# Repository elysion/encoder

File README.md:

# Interface module for modular controllers

The module can be used for converting encoder, pot and button movement
into messages sent over TWI / I2C. You can e.g. combine up to 6 encoders 
(with push buttons) and connect them to a single 
microcontroller (ATMega168p) using only two separate PCB designs. This 
helps to bring down the costs of the BOM and of the boards. The design 
also  includes a configurable LED ring that can be used to visualize the 
positions of the encoders. You can connect up to 112 microcontroller 
boards to a single bus to create a device with up to 672 encoders!

By connecting a USB enabled microcontroller to the I2C bus you can
create an UI for all kinds of devices such as musical instruments,
DJ controllers, home automation control panels, etc.

The PCBs are connected using FFC cables making building, reusing
reconfiguring and debugging the parts easy while at the same time
keeping the BOM cost low.

You can find a proof of concept programming jig / bed of nails tester
for the microcontroller board here: https://a360.co/2ylXmQ3

## Currently supported components and settings
* Encoders
  * Absolute / Relative
  * Loop around / constrained between values
* Potentiometers
* Single switches and 3x3 button matrices
* AT42QT1010 capacitive touch sensor
* Sparkfun 2x2 button pads with SMT LED
* SK6812 / WS2812 serially addressable LEDs

## Project status
* If you would like to use the designs and the code in your project, please add a issue to this repository
  so that I can check whether the needed features have been implemented.
* There have been multiple iterations of the PCBs and not all software has been updated to work on the
  latest PCBs. The current implementation uses the PCB_VERSION constant with value 3 in the code.
  * Features not updated currently:
    * Touch
    * Pads
    * Potentiometers
    * Button matrices (?)

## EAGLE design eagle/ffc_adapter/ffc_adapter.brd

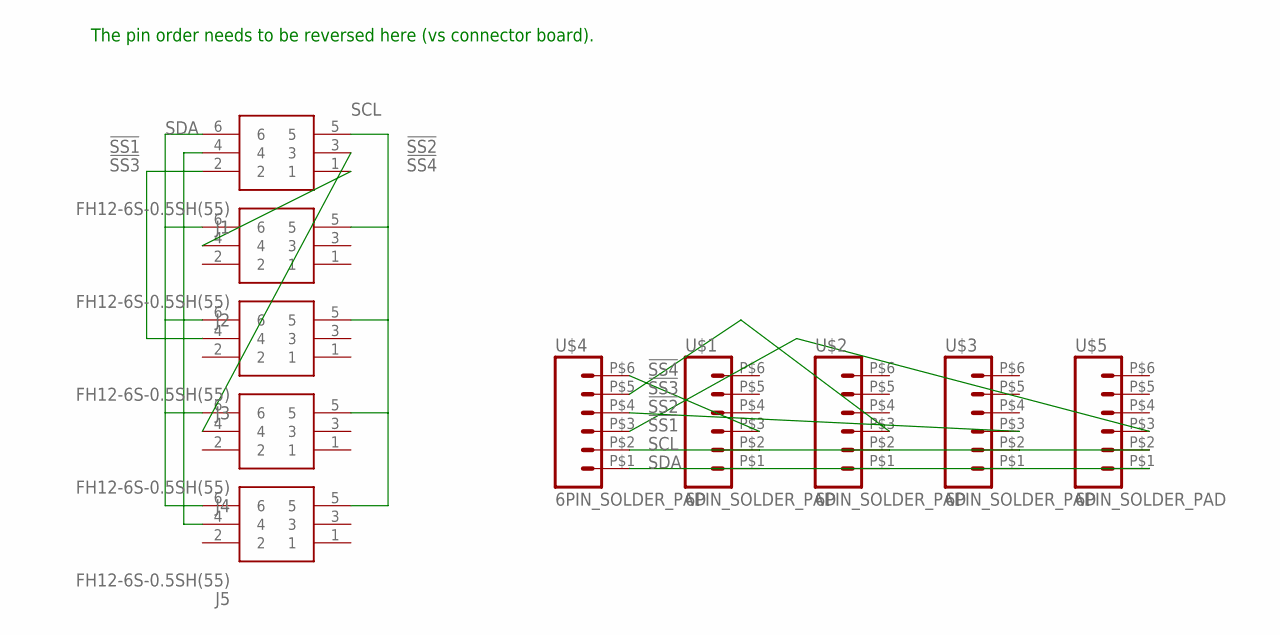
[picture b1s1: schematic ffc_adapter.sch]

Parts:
J1, J2, J3, J4, J5: FH12-6S-0.5SH(55); FH12-6S-0.5SH(55)_1
U$1, U$2, U$3, U$4, U$5: 6PIN_SOLDER_PAD

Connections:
!SS1: J1.4, J5.4, U$4.P$3 (3), U$5.P$3 (3)
!SS2: J1.3, J4.4, U$3.P$3 (3), U$4.P$4 (4)
!SS3: J1.2, J3.4, U$2.P$3 (3), U$4.P$5 (5)
!SS4: J1.1, J2.4, U$1.P$3 (3), U$4.P$6 (6)
SCL: J1.5, J2.5, J3.5, J4.5, J5.5, U$1.P$2 (2), U$2.P$2 (2), U$3.P$2 (2), U$4.P$2 (2), U$5.P$2 (2)
SDA: J1.6, J2.6, J3.6, J4.6, J5.6, U$1.P$1 (1), U$2.P$1 (1), U$3.P$1 (1), U$4.P$1 (1), U$5.P$1 (1)

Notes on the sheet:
The pin order needs to be reversed here (vs connector board).

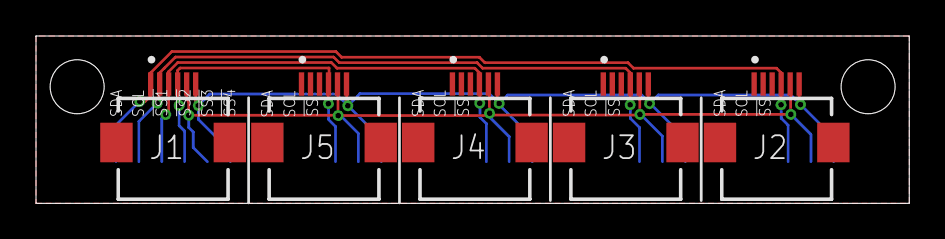
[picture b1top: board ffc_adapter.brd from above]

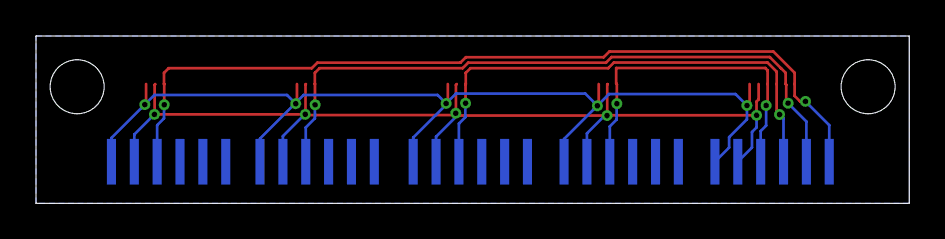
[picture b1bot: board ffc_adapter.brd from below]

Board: 2 copper layers, 48.5 x 9.3 mm, 10 parts (5 on the bottom side), 6 nets.

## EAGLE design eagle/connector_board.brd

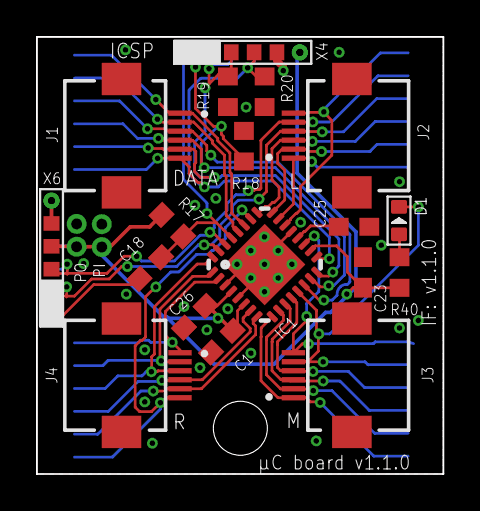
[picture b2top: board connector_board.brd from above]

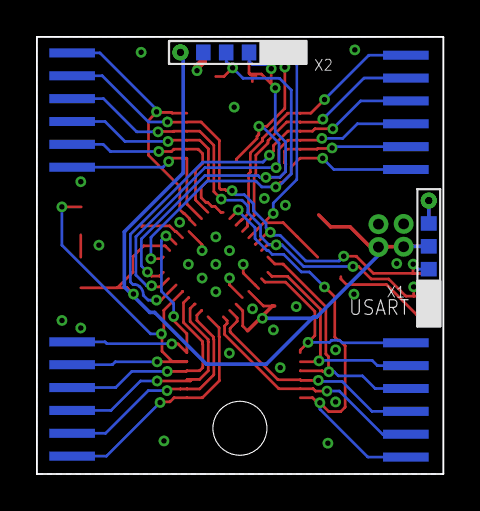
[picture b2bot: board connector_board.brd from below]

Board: 2 copper layers, 22.6 x 24.3 mm, 28 parts (6 on the bottom side), 32 nets.

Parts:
C1, C18, C23, C25, C26: 100n; C0603
D1: RED-0603; LED-0603
IC1: MEGA8-MI; MLF32-TH
J1, J2, J3, J4: FH12-6S-0.5SH(55); FH12-6S-0.5SH(55)_1
PI: 2PIN_1.27MM; 1X02_1.27MM_NO_SILK
PO: 2PIN_1.27MM; 1X02_1.27MM_NO_SILK
R17, R40: 10k; R0603
R18, R19, R20: R0603
SH1, SH2: SHORT; SHORT_TOP_8MIL
U$1, U$2, U$3, U$4: 6PIN_SOLDER_PAD
X1, X2, X4, X6: POGOPIN-CONNWITHVIAS-SMV; POGOPROG-CONN-OH-SMALLERVIAS

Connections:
!RESET: C18.2, IC1.29, R17.1, X2.1, X4.1
!SS: IC1.14, J1.3, U$4.P$4
AREF: C25.1, IC1.20
DTR: C18.1, X1.1, X6.1
ENCL1A: IC1.23, J2.1, U$3.P$6
ENCL1B: IC1.24, J2.2, U$3.P$5
ENCL2A: IC1.31, J2.4, SH2.P$1, U$3.P$3
ENCL2B: IC1.30, J2.5, SH1.P$1, U$3.P$2
ENCM1A: IC1.9, J3.1, U$1.P$6
ENCM1B: IC1.10, J3.2, U$1.P$5
ENCM2A: IC1.12, J3.4, U$1.P$3
ENCM2B: D1.-, IC1.13, J3.5, U$1.P$2
ENCR1A: IC1.2, J4.1, U$2.P$6
ENCR1B: IC1.1, J4.2, U$2.P$5
ENCR2A: IC1.7, J4.4, U$2.P$3
ENCR2B: IC1.8, J4.5, U$2.P$2
GND: C1.2, C23.2, C25.2, C26.2, IC1.3, IC1.5, IC1.21, IC1.TH, PI.10, PO.10, R18.2, R19.2, R20.2, X1.5, X1.6, X2.5, X4.5, X6.5, X6.6
LEDL: IC1.25, J2.3, U$3.P$4
LEDM: IC1.11, J3.3, U$1.P$4
LEDR: IC1.32, J4.3, U$2.P$4
MISO: IC1.16, J1.5, R19.1, U$4.P$2, X2.3, X4.3
MOSI: IC1.15, J1.4, R18.1, U$4.P$3, X2.2, X4.2
unnamed: D1.+, R40.2
RXD: SH1.P$2, X1.3, X6.3
SCK: IC1.17, J1.6, R20.1, U$4.P$1, X2.4, X4.4
SCL: IC1.28, J1.2, U$4.P$5
SDA: IC1.27, J1.1, U$4.P$6
SWL: IC1.22, J2.6, U$3.P$1
SWM: IC1.19, J3.6, U$1.P$1
SWR: IC1.26, J4.6, U$2.P$1
TXD: SH2.P$2, X1.2, X6.2
VCC: C1.1, C23.1, C26.1, IC1.4, IC1.6, IC1.18, PI.9, PO.9, R17.2, R40.1, X1.4, X2.6, X4.6, X6.4

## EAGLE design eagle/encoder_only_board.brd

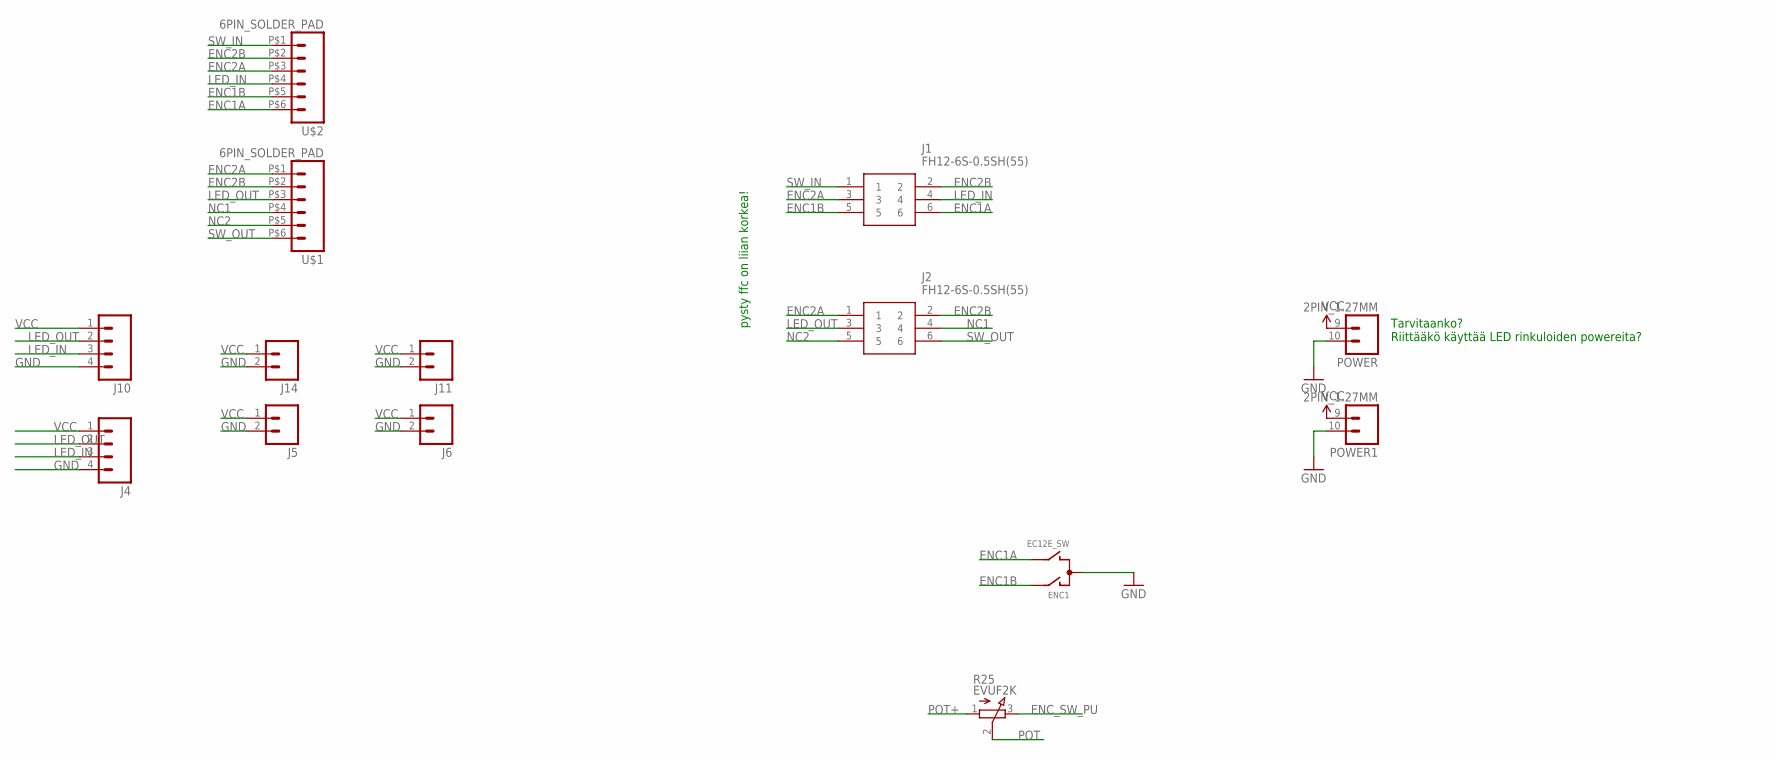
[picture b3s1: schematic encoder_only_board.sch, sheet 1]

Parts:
ENC1: EC12E_SW; ALPS_EC12E_SW
J1, J2: FH12-6S-0.5SH(55); FH12-6S-0.5SH(55)_1
J4, J10: M04NO_SILK_ALL_ROUND; 1X04_NO_SILK_ALL_ROUND
J5, J6, J11, J14: M021X02_NO_SILK; 1X02_NO_SILK
POWER, POWER1: 2PIN_1.27MM; 1X02_1.27MM_NO_SILK
R25: EVUF2K; EVUFXK
U$1, U$2: 6PIN_SOLDER_PAD

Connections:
ENC1A: ENC1.B, J1.6, U$2.P$6 (6)
ENC1B: ENC1.A, J1.5, U$2.P$5 (5)
ENC2A: J1.3, J2.1, U$1.P$1 (1), U$2.P$3 (3); also elsewhere on the board
ENC2B: J1.2, J2.2, U$1.P$2 (2), U$2.P$2 (2); also elsewhere on the board
ENC_SW_PU: R25.3 (E); also elsewhere on the board
GND: ENC1.C, J4.4, J5.2, J6.2, J10.4, J11.2, J14.2, POWER.10 (2), POWER1.10 (2); also elsewhere on the board
LED_IN: J1.4, J4.3, J10.3, U$2.P$4 (4); also elsewhere on the board
LED_OUT: J2.3, J4.2, J10.2, U$1.P$3 (3); also elsewhere on the board
NC1: J2.4, U$1.P$4 (4)
NC2: J2.5, U$1.P$5 (5)
POT: R25.2 (S); also elsewhere on the board
POT+: R25.1 (A); also elsewhere on the board
SW_IN: J1.1, U$2.P$1 (1); also elsewhere on the board
SW_OUT: J2.6, U$1.P$6 (6); also elsewhere on the board
VCC: J4.1, J5.1, J6.1, J10.1, J11.1, J14.1, POWER.9 (1), POWER1.9 (1); also elsewhere on the board

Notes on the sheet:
Tarvitaanko? Riittääkö käyttää LED rinkuloiden powereita?
pysty ffc on liian korkea!

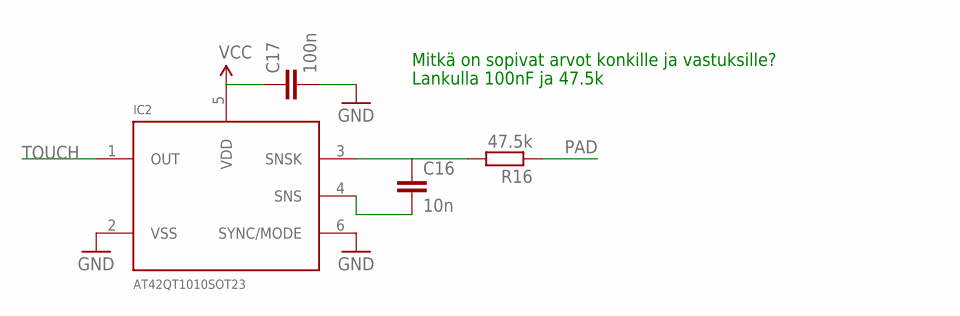
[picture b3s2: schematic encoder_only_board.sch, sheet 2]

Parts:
C16: 10n; 0603-CAP
C17: 100n; 0603-CAP
IC2: AT42QT1010SOT23; SOT23-6
R16: 47.5k; R0603

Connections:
GND: C17.2, IC2.2 (VSS), IC2.6 (SYNC/MODE); also elsewhere on the board
unnamed: C16.1, IC2.3 (SNSK), R16.2
unnamed: C16.2, IC2.4 (SNS)
PAD: R16.1
TOUCH: IC2.1 (OUT); also elsewhere on the board
VCC: C17.1, IC2.5 (VDD); also elsewhere on the board

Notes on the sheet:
Mitkä on sopivat arvot konkille ja vastuksille?
Lankulla 100nF ja 47.5k

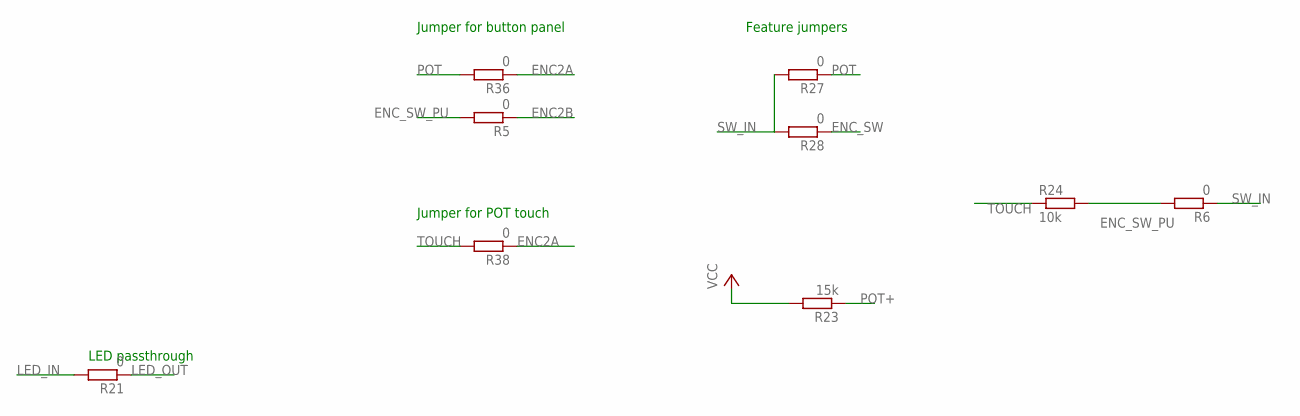
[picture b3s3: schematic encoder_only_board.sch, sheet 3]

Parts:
R5, R6, R21, R27, R28, R36, R38: 0; R0603
R23: 15k; R0603
R24: 10k; R0603

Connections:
ENC2A: R36.1, R38.1; also elsewhere on the board
ENC2B: R5.1; also elsewhere on the board
ENC_SW: R28.1; also elsewhere on the board
ENC_SW_PU: R5.2, R6.2, R24.2; also elsewhere on the board
LED_IN: R21.2; also elsewhere on the board
LED_OUT: R21.1; also elsewhere on the board
POT: R27.1, R36.2; also elsewhere on the board
POT+: R23.1; also elsewhere on the board
SW_IN: R6.1, R27.2, R28.2; also elsewhere on the board
TOUCH: R24.1, R38.2; also elsewhere on the board
VCC: R23.2; also elsewhere on the board

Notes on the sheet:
LED passthrough
Jumper for button panel
Jumper for POT touch
Feature jumpers

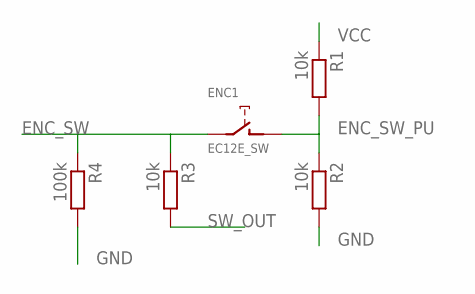
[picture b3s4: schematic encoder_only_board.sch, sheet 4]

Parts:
ENC1: EC12E_SW; ALPS_EC12E_SW
R1, R2, R3: 10k; R0603
R4: 100k; R0603

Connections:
ENC_SW: ENC1.E (2), R3.1, R4.1; also elsewhere on the board
ENC_SW_PU: ENC1.D (1), R1.2, R2.1; also elsewhere on the board
GND: R2.2, R4.2; also elsewhere on the board
SW_OUT: R3.2; also elsewhere on the board
VCC: R1.1; also elsewhere on the board

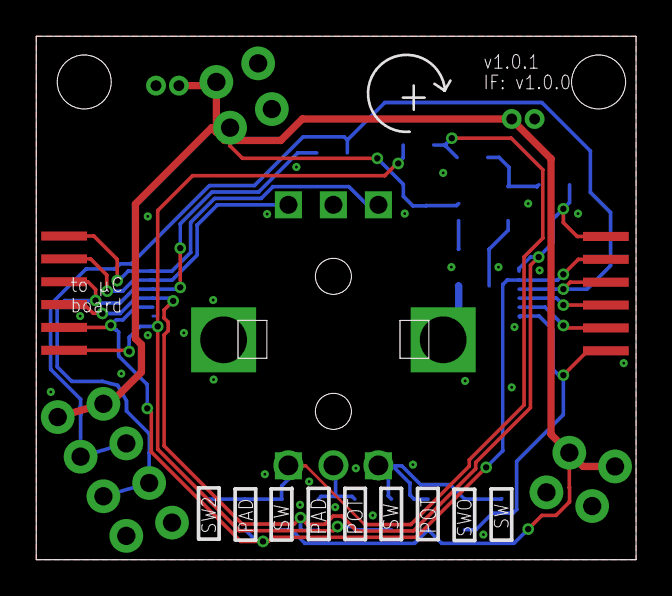
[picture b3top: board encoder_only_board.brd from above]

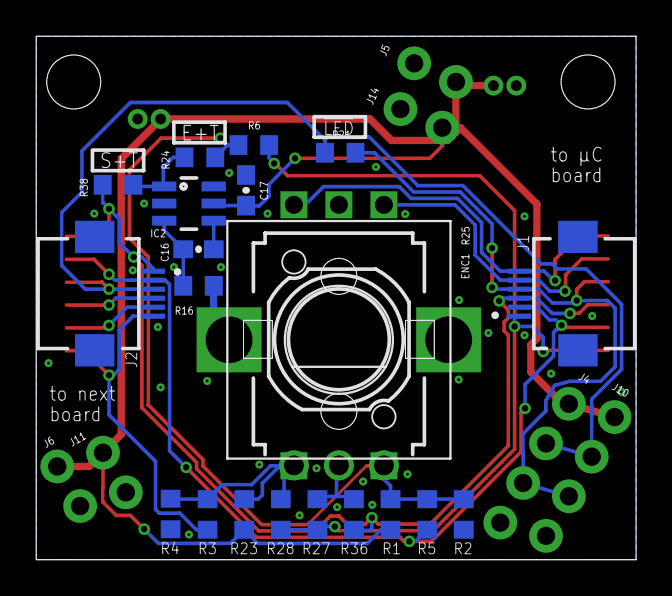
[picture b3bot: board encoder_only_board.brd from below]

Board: 2 copper layers, 33.3 x 29.1 mm, 31 parts (28 on the bottom side), 19 nets.

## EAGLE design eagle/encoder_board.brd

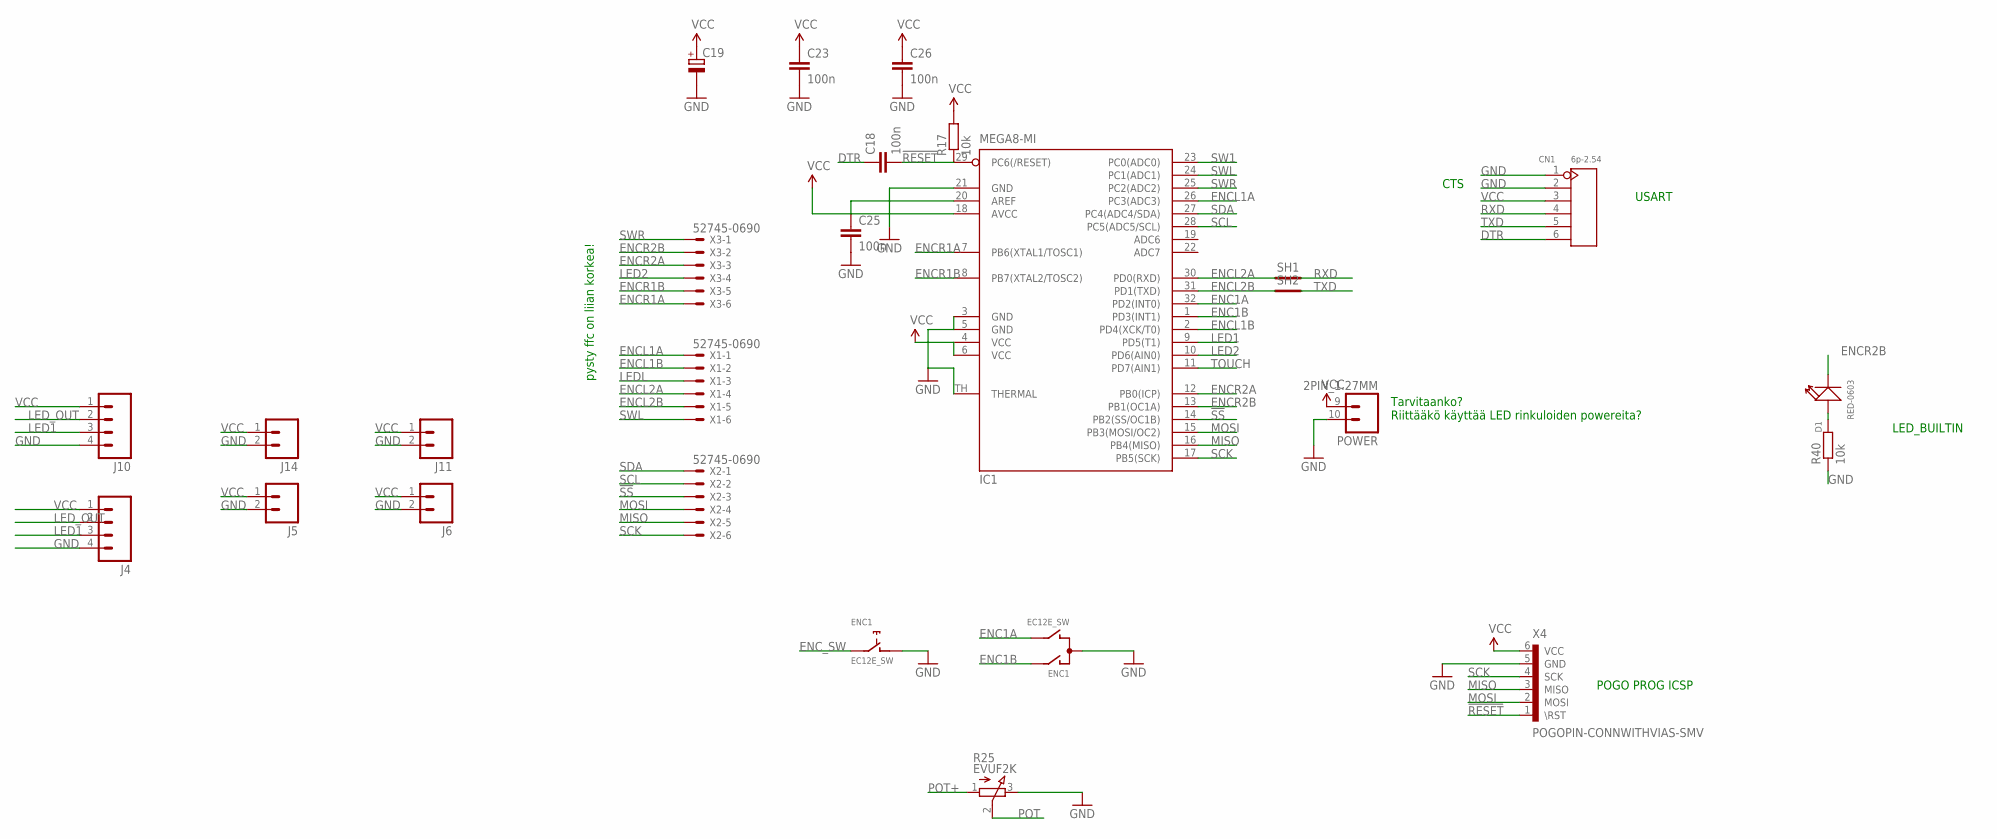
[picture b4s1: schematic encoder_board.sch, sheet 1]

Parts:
C18, C23, C25, C26: 100n; 0603-CAP
C19: CPOL-EUC; PANASONIC_C
CN1: 6p-2.54; H6-2.54
D1: RED-0603; LED-0603
ENC1: EC12E_SW; ALPS_EC12E_SW
IC1: MEGA8-MI; MLF32-TH
J4, J10: M04NO_SILK_ALL_ROUND; 1X04_NO_SILK_ALL_ROUND
J5, J6, J11, J14: M021X02_NO_SILK; 1X02_NO_SILK
POWER: 2PIN_1.27MM; 1X02_1.27MM_NO_SILK
R17, R40: 10k; R0603
R25: EVUF2K; EVUFXK
SH1, SH2: SHORT; SHORT_TOP_8MIL
X1, X2, X3: 52745-0690
X4: POGOPIN-CONNWITHVIAS-SMV; POGOPROG-CONN-OH-SMALLERVIAS

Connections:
!RESET: C18.2, IC1.29 (PC6(/RESET)), R17.1, X4.1 (\RST)
!SS: IC1.14 (PB2(SS/OC1B)), X2.3
AREF: C25.1, IC1.20 (AREF)
DTR: C18.1, CN1.6
ENC1A: ENC1.B, IC1.32 (PD2(INT0)); also elsewhere on the board
ENC1B: ENC1.A, IC1.1 (PD3(INT1)); also elsewhere on the board
ENCL1A: IC1.26 (PC3(ADC3)), X1.1; also elsewhere on the board
ENCL1B: IC1.2 (PD4(XCK/T0)), X1.2; also elsewhere on the board
ENCL2A: IC1.30 (PD0(RXD)), SH1.P$1, X1.4; also elsewhere on the board
ENCL2B: IC1.31 (PD1(TXD)), SH2.P$1, X1.5; also elsewhere on the board
ENCR1A: IC1.7 (PB6(XTAL1/TOSC1)), X3.6; also elsewhere on the board
ENCR1B: IC1.8 (PB7(XTAL2/TOSC2)), X3.5; also elsewhere on the board
ENCR2A: IC1.12 (PB0(ICP)), X3.3; also elsewhere on the board
ENCR2B: D1.-, IC1.13 (PB1(OC1A)), X3.2; also elsewhere on the board
ENC_SW: ENC1.E (2); also elsewhere on the board
GND: C19.-, C23.2, C25.2, C26.2, CN1.1, CN1.2, ENC1.C, ENC1.D (1), IC1.3 (GND), IC1.5 (GND), IC1.21 (GND), IC1.TH (THERMAL), J4.4, J5.2, J6.2, J10.4, J11.2, J14.2, POWER.10 (2), R25.3 (E), R40.1, X4.5 (GND); also elsewhere on the board
LED1: IC1.9 (PD5(T1)), J4.3, J10.3; also elsewhere on the board
LED2: IC1.10 (PD6(AIN0)), X3.4; also elsewhere on the board
LEDL: X1.3; also elsewhere on the board
LED_OUT: J4.2, J10.2; also elsewhere on the board
MISO: IC1.16 (PB4(MISO)), X2.5, X4.3 (MISO); also elsewhere on the board
MOSI: IC1.15 (PB3(MOSI/OC2)), X2.4, X4.2 (MOSI); also elsewhere on the board
unnamed: D1.+, R40.2
POT: R25.2 (S); also elsewhere on the board
POT+: R25.1 (A); also elsewhere on the board
RXD: CN1.4, SH1.P$2
SCK: IC1.17 (PB5(SCK)), X2.6, X4.4 (SCK); also elsewhere on the board
SCL: IC1.28 (PC5(ADC5/SCL)), X2.2
SDA: IC1.27 (PC4(ADC4/SDA)), X2.1
SW1: IC1.23 (PC0(ADC0)); also elsewhere on the board
SWL: IC1.24 (PC1(ADC1)), X1.6; also elsewhere on the board
SWR: IC1.25 (PC2(ADC2)), X3.1; also elsewhere on the board
TOUCH: IC1.11 (PD7(AIN1)); also elsewhere on the board
TXD: CN1.5, SH2.P$2
VCC: C19.+, C23.1, C26.1, CN1.3, IC1.4 (VCC), IC1.6 (VCC), IC1.18 (AVCC), J4.1, J5.1, J6.1, J10.1, J11.1, J14.1, POWER.9 (1), R17.2, X4.6 (VCC); also elsewhere on the board

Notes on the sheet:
CTS
Tarvitaanko? Riittääkö käyttää LED rinkuloiden powereita?
USART
POGO PROG ICSP
pysty ffc on liian korkea!
LED_BUILTIN

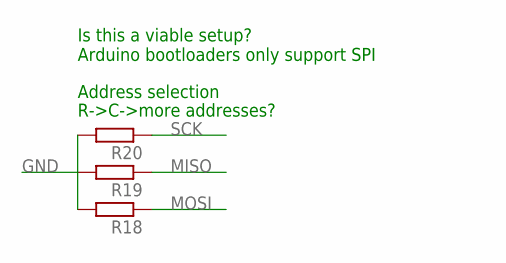
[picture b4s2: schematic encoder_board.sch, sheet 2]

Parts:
R18, R19, R20: R-EU_R0603; R0603

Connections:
GND: R18.2, R19.2, R20.2; also elsewhere on the board
MISO: R19.1; also elsewhere on the board
MOSI: R18.1; also elsewhere on the board
SCK: R20.1; also elsewhere on the board

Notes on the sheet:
Address selection
R->C->more addresses?
Is this a viable setup? Arduino bootloaders only support SPI

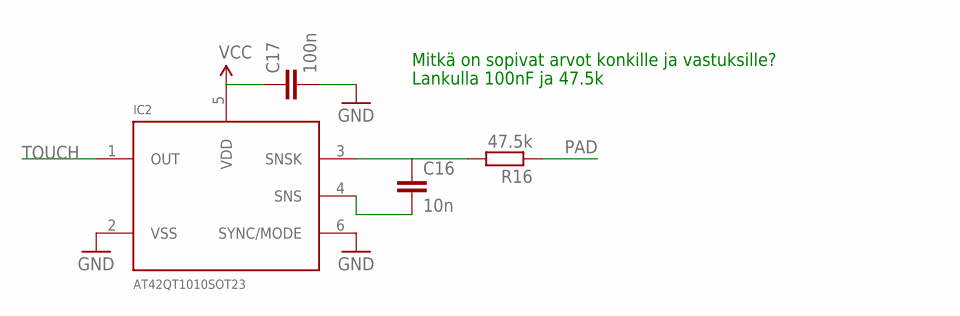
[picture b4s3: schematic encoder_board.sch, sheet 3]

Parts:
C16: 10n; 0603-CAP
C17: 100n; 0603-CAP
IC2: AT42QT1010SOT23; SOT23-6
R16: 47.5k; R0603

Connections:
GND: C17.2, IC2.2 (VSS), IC2.6 (SYNC/MODE); also elsewhere on the board
unnamed: C16.1, IC2.3 (SNSK), R16.2
unnamed: C16.2, IC2.4 (SNS)
PAD: R16.1
TOUCH: IC2.1 (OUT); also elsewhere on the board
VCC: C17.1, IC2.5 (VDD); also elsewhere on the board

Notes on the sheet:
Mitkä on sopivat arvot konkille ja vastuksille?
Lankulla 100nF ja 47.5k

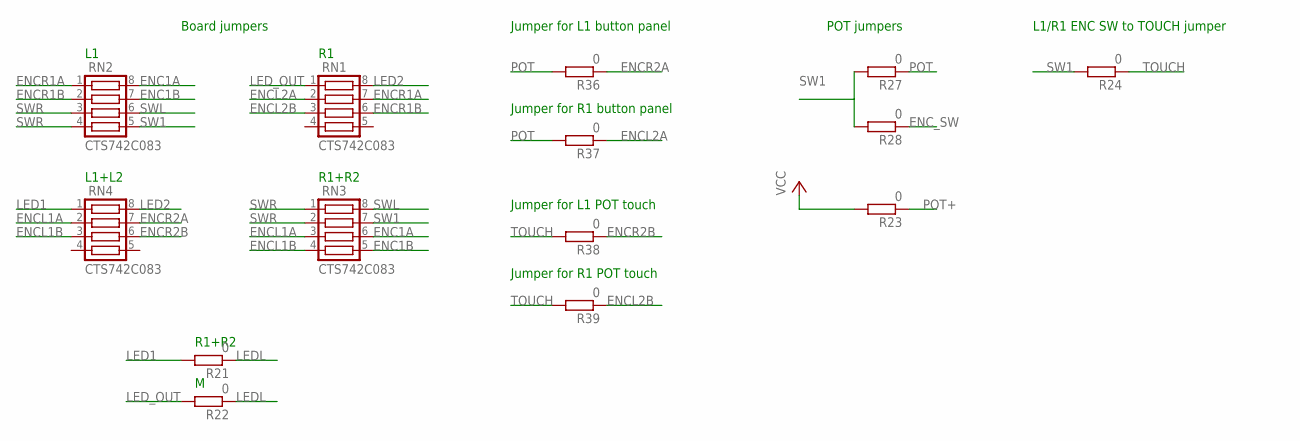
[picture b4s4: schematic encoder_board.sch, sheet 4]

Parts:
R21, R22, R23, R24, R27, R28, R36, R37, R38, R39: 0; R0603
RN1, RN2, RN3, RN4: CTS742C083

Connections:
ENC1A: RN2.8, RN3.6; also elsewhere on the board
ENC1B: RN2.7, RN3.5; also elsewhere on the board
ENCL1A: RN3.3, RN4.2; also elsewhere on the board
ENCL1B: RN3.4, RN4.3; also elsewhere on the board
ENCL2A: R37.1, RN1.2; also elsewhere on the board
ENCL2B: R39.1, RN1.3; also elsewhere on the board
ENCR1A: RN1.7, RN2.1; also elsewhere on the board
ENCR1B: RN1.6, RN2.2; also elsewhere on the board
ENCR2A: R36.1, RN4.7; also elsewhere on the board
ENCR2B: R38.1, RN4.6; also elsewhere on the board
ENC_SW: R28.1; also elsewhere on the board
LED1: R21.2, RN4.1; also elsewhere on the board
LED2: RN1.8, RN4.8; also elsewhere on the board
LEDL: R21.1, R22.1; also elsewhere on the board
LED_OUT: R22.2, RN1.1; also elsewhere on the board
POT: R27.1, R36.2, R37.2; also elsewhere on the board
POT+: R23.1; also elsewhere on the board
SW1: R24.2, R27.2, R28.2, RN2.5, RN3.7; also elsewhere on the board
SWL: RN2.6, RN3.8; also elsewhere on the board
SWR: RN2.3, RN2.4, RN3.1, RN3.2; also elsewhere on the board
TOUCH: R24.1, R38.2, R39.2; also elsewhere on the board
VCC: R23.2; also elsewhere on the board

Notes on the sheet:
R1+R2
L1/R1 ENC SW to TOUCH jumper
Jumper for L1 button panel
Jumper for R1 button panel
Jumper for L1 POT touch
Jumper for R1 POT touch
L1+L2
Board jumpers
POT jumpers

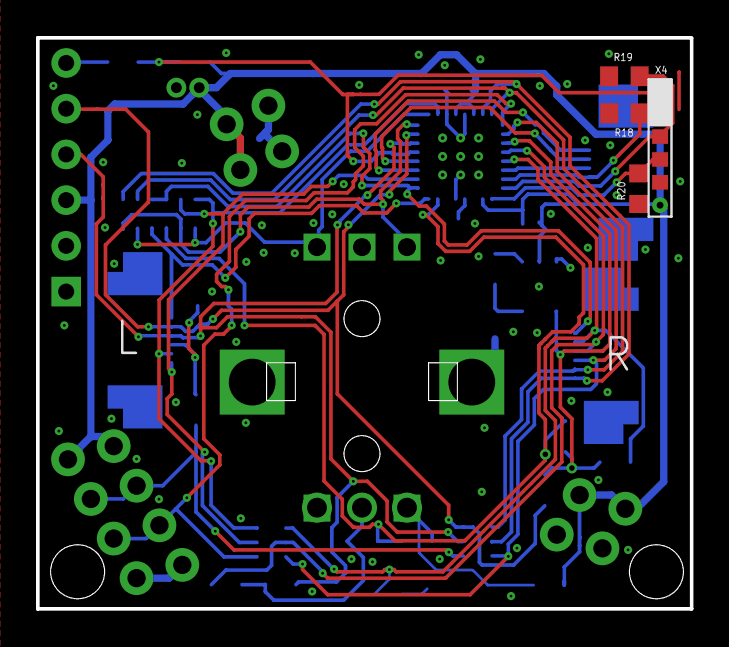
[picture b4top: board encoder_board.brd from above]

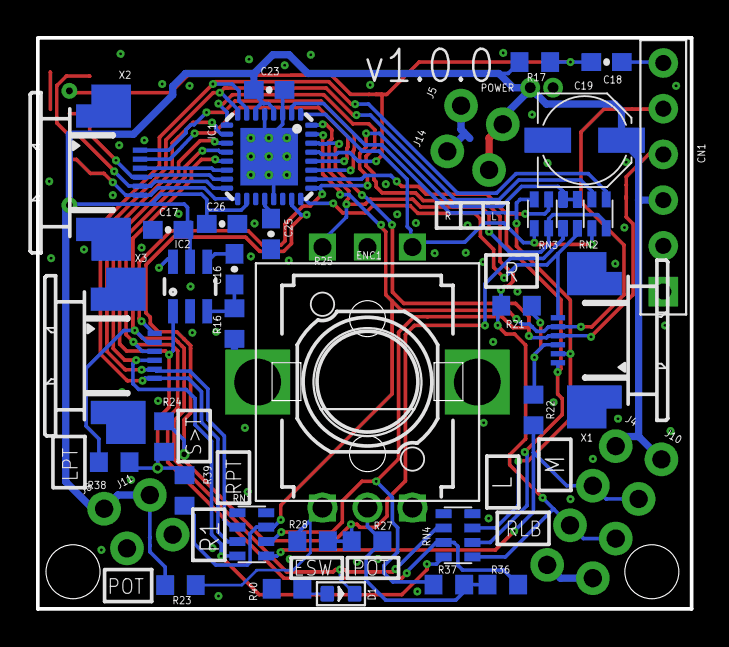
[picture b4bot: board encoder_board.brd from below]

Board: 2 copper layers, 36.3 x 31.7 mm, 46 parts (40 on the bottom side), 37 nets.

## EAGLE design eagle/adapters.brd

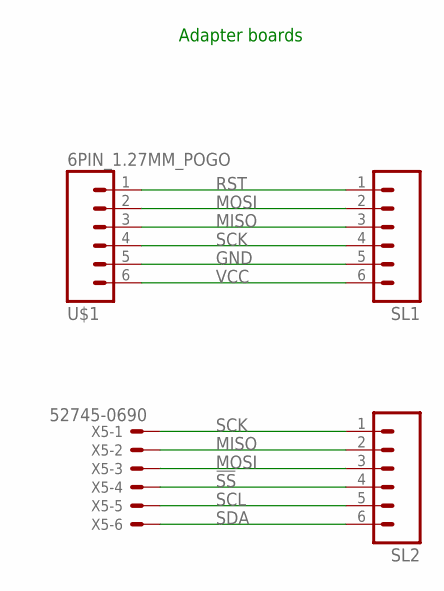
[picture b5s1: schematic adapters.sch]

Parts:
SL1, SL2: M06; 06P
U$1: 6PIN_1.27MM_POGO; 1X06-1.27MM_POGO
X5: 52745-0690

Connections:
!SS: SL2.4, X5.4
GND: SL1.5, U$1.5
MISO: SL1.3, SL2.2, U$1.3, X5.2
MOSI: SL1.2, SL2.3, U$1.2, X5.3
RST: SL1.1, U$1.1
SCK: SL1.4, SL2.1, U$1.4, X5.1
SCL: SL2.5, X5.5
SDA: SL2.6, X5.6
VCC: SL1.6, U$1.6

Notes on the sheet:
Adapter boards

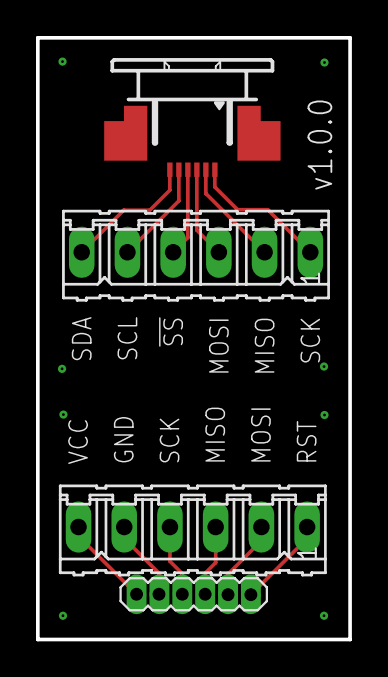
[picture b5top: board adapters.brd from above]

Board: 2 copper layers, 17.3 x 33.4 mm, 4 parts (0 on the bottom side), 9 nets.

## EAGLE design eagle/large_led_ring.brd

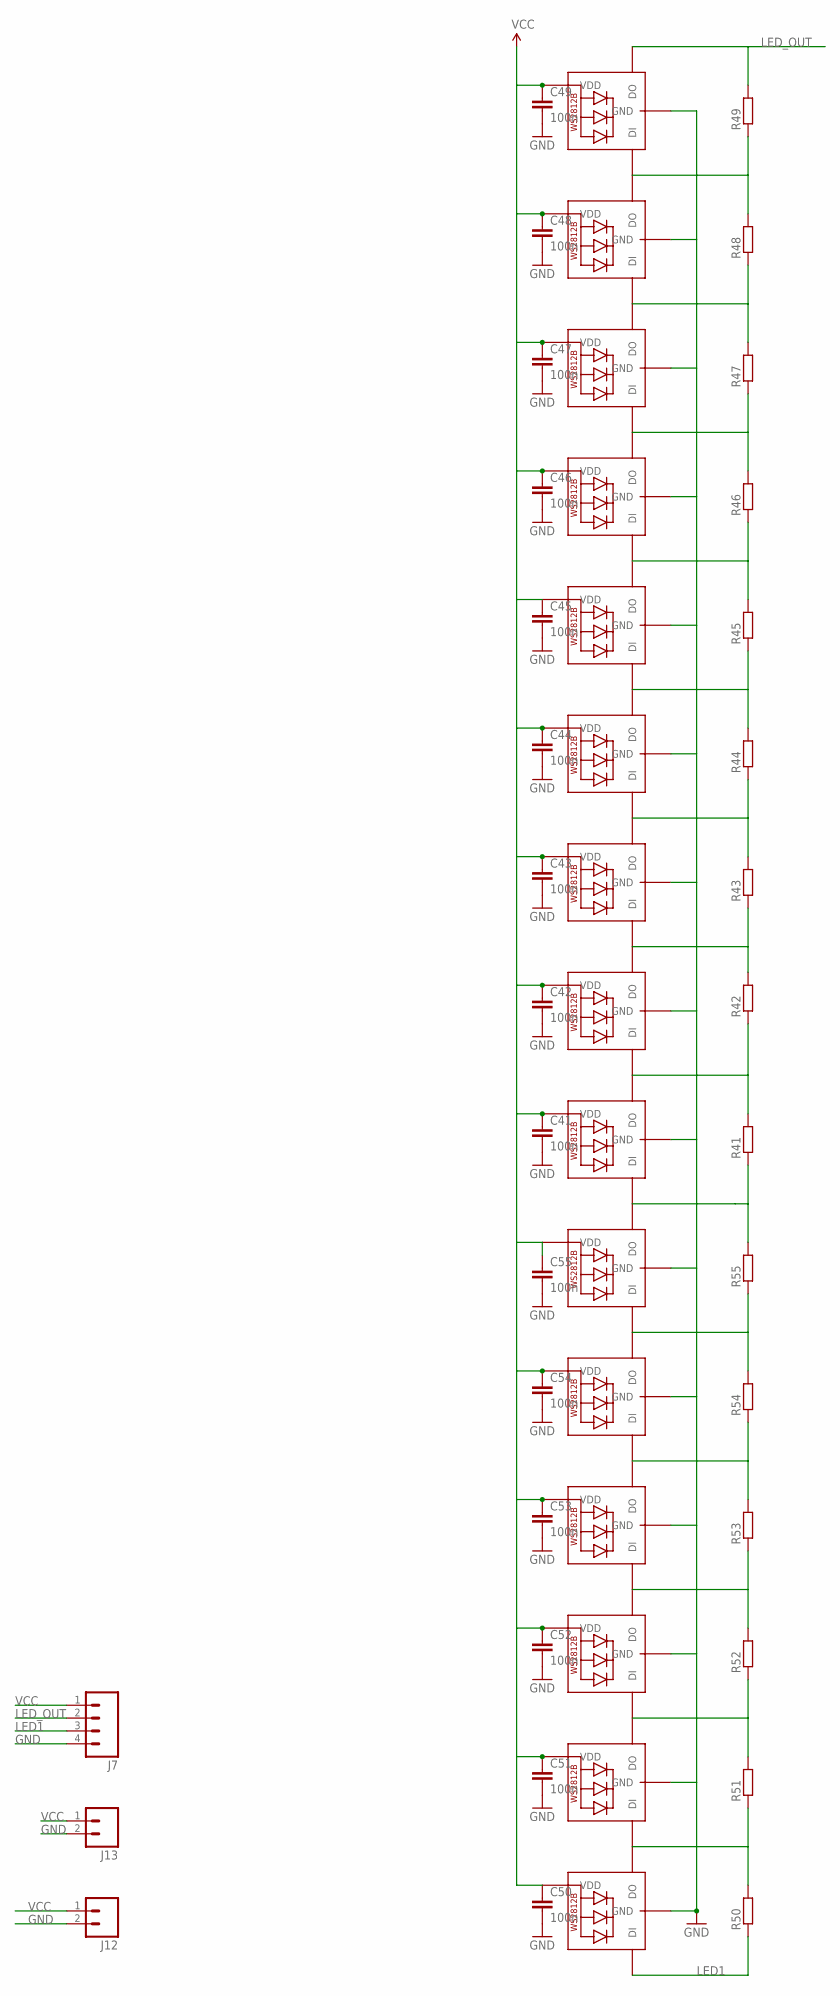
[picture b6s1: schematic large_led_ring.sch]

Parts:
C41, C42, C43, C44, C45, C46, C47, C48, C49, C50, C51, C52, C53, C54, C55: 100n; 0603-CAP
J7: M04NO_SILK_ALL_ROUND; 1X04_NO_SILK_ALL_ROUND
J12, J13: M021X02_NO_SILK; 1X02_NO_SILK
LED31, LED32, LED33, LED34, LED35, LED36, LED37, LED38, LED39, LED40, LED41, LED42, LED43, LED44, LED45: WS2812B3535; LED3535
R41, R42, R43, R44, R45, R46, R47, R48, R49, R50, R51, R52, R53, R54, R55: R-EU_R0603; R0603

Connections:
GND: C41.2, C42.2, C43.2, C44.2, C45.2, C46.2, C47.2, C48.2, C49.2, C50.2, C51.2, C52.2, C53.2, C54.2, C55.2, J7.4, J12.2, J13.2, LED31.4 (GND), LED32.4 (GND), LED33.4 (GND), LED34.4 (GND), LED35.4 (GND), LED36.4 (GND), LED37.4 (GND), LED38.4 (GND), LED39.4 (GND), LED40.4 (GND), LED41.4 (GND), LED42.4 (GND), LED43.4 (GND), LED44.4 (GND), LED45.4 (GND)
LED1: J7.3, LED31.1 (DI), R50.1
LED_OUT: J7.2, LED45.3 (DO), R49.2
unnamed: LED37.3 (DO), LED38.1 (DI), R41.2, R42.1
unnamed: LED38.3 (DO), LED39.1 (DI), R42.2, R43.1
unnamed: LED39.3 (DO), LED40.1 (DI), R43.2, R44.1
unnamed: LED42.3 (DO), LED43.1 (DI), R46.2, R47.1
unnamed: LED43.3 (DO), LED44.1 (DI), R47.2, R48.1
unnamed: LED44.3 (DO), LED45.1 (DI), R48.2, R49.1
unnamed: LED32.3 (DO), LED33.1 (DI), R51.2, R52.1
unnamed: LED33.3 (DO), LED34.1 (DI), R52.2, R53.1
unnamed: LED34.3 (DO), LED35.1 (DI), R53.2, R54.1
unnamed: LED35.3 (DO), LED36.1 (DI), R54.2, R55.1
unnamed: LED31.3 (DO), LED32.1 (DI), R50.2, R51.1
unnamed: LED40.3 (DO), LED41.1 (DI), R44.2, R45.1
unnamed: LED41.3 (DO), LED42.1 (DI), R45.2, R46.1
unnamed: LED36.3 (DO), LED37.1 (DI), R41.1, R55.2
VCC: C41.1, C42.1, C43.1, C44.1, C45.1, C46.1, C47.1, C48.1, C49.1, C50.1, C51.1, C52.1, C53.1, C54.1, C55.1, J7.1, J12.1, J13.1, LED31.2 (VDD), LED32.2 (VDD), LED33.2 (VDD), LED34.2 (VDD), LED35.2 (VDD), LED36.2 (VDD), LED37.2 (VDD), LED38.2 (VDD), LED39.2 (VDD), LED40.2 (VDD), LED41.2 (VDD), LED42.2 (VDD), LED43.2 (VDD), LED44.2 (VDD), LED45.2 (VDD)

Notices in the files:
arduino/hardware/elysion/avr/variants/encoder/pins_arduino.h:
Copyright (c) 2007 David A. Mellis
Public License along with this library; if not, write to the
Free Software Foundation, Inc., 59 Temple Place, Suite 330,
Boston, MA  02111-1307  USA
parts and their libraries:
edge: Licensing: Creative Commons ShareAlike 4.0 International - https://creativecommons.org/licenses/by-sa/4.0
